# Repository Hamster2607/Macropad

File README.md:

This Macropad has 6 keys for media control and microphone with a rotary encoder for scrolling with qmk firmware. It also has an OLED display.

## Features

  -scrolling up/down
  -muting/unmuting the microphone
  -controlling media(e.g. skip track, pause, previous track)

## BOM
  
| Part                  | Quantity | Price (each) | Total   | Notes                        

 Seeed XIAO RP2040      1       | $6.50        | $6.50   Main MCU                      
 Switches with keycaps  5       | $0.50        | $2.50   TS-style, direct pin          
 Rotary encoder w/button  1     | $1.20        | $1.20   3-pin encoder                 
 3D-printed case        1 set   | $2.00        | $2.00   PLA, ~50 g 
 
Total : ~12.20 USD

## Layout

| SW1 (Undo) | SW2 (Prev) | SW6 (Next) |

| S1 (Mute)  | SW4 (Enter)| SW5 (Play) |

## PCB
This is the schematic for the PCB, made in KiCad

And this is the footprint

## Case

The case will be held tight by 4 M3x16 mm screws and it can be fuly 3D printed

## Full assembly(couldn't put switches in the model, get a hold of your imagination)

The XIAO RP2040 will stay under the PCB, to save space while being fully accessible trough the side

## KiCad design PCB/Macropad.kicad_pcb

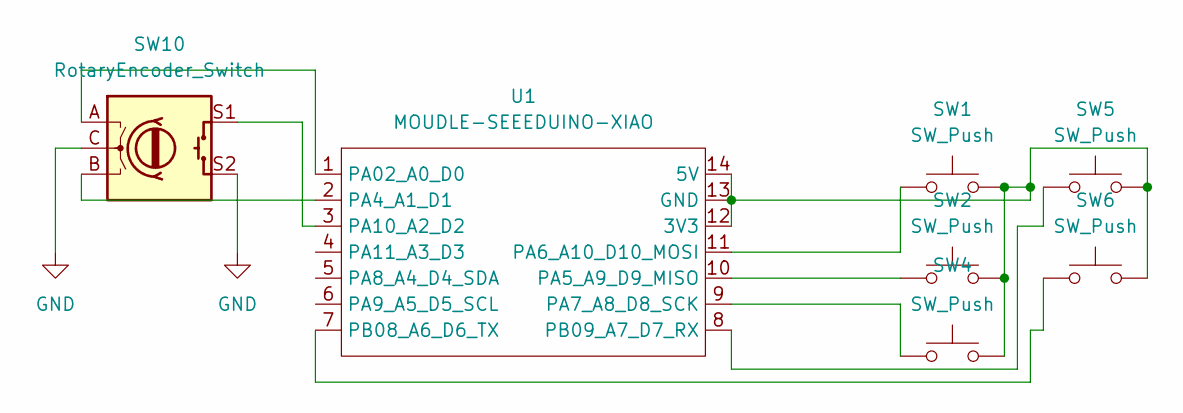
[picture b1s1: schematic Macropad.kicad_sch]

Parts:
SW1, SW2, SW4, SW5, SW6: SW_Push; SW_Cherry_MX_1.00u_PCB
SW10: RotaryEncoder_Switch; RotaryEncoder_Alps_EC11E-Switch_Vertical_H20mm
U1: MOUDLE-SEEEDUINO-XIAO; XIAO-Generic-Hybrid-14P-2.54-21X17.8MM

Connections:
GND: SW10.C, SW10.S2
unnamed: SW1.2, SW2.2, SW4.2, SW5.2, SW6.2, U1.12 (3V3), U1.13 (GND), U1.14 (5V)
unnamed: SW10.A, U1.1 (PA02_A0_D0)
unnamed: SW10.B, U1.2 (PA4_A1_D1)
unnamed: SW2.1, U1.10 (PA5_A9_D9_MISO)
unnamed: SW1.1, U1.11 (PA6_A10_D10_MOSI)
unnamed: SW4.1, U1.9 (PA7_A8_D8_SCK)
unnamed: SW10.S1, U1.3 (PA10_A2_D2)
unnamed: SW6.1, U1.7 (PB08_A6_D6_TX)
unnamed: SW5.1, U1.8 (PB09_A7_D7_RX)

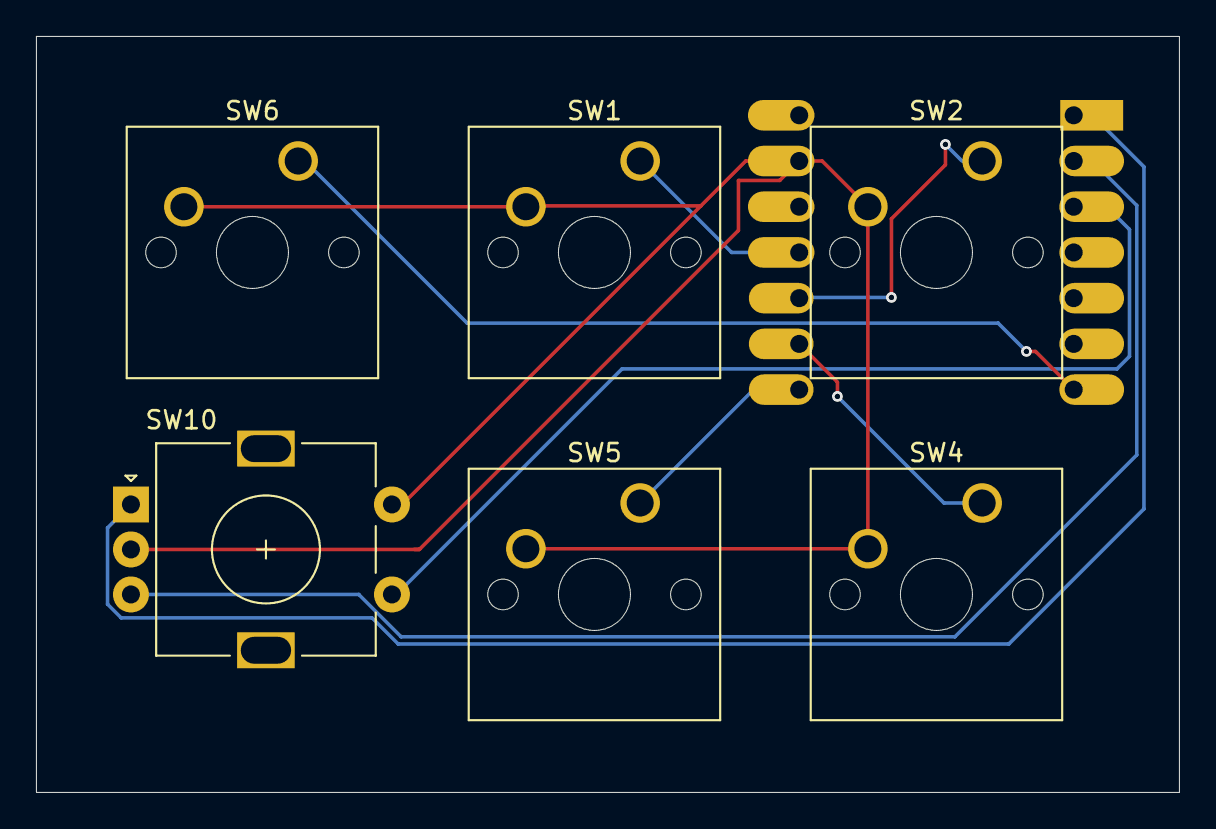
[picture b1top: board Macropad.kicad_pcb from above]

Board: 2 copper layers, 63.5 x 42.0 mm, 7 parts (1 on the bottom side), 10 nets.

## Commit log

2026-02-19 Fixed names
2026-02-19 Fixed names again....
2026-02-20 Added the compiled firmware and also the source code
2026-02-20 Added a readme
    Added detailed information about the Macropad project, including features, BOM, layout, PCB schematics, and case design.
2026-02-20 Fix image paths in README.md
    Updated image references for schematic, footprint, and case in README.
2026-02-20 Fix image references in README.md
2026-02-20 New case
2026-02-23 Case design update, PCB tweaks
2026-02-23 Add full assembly section to README
    Added section on full assembly with images.
2026-02-23 Updated Readme
    Added note about the XIAO RP2040 placement under the PCB.
2026-02-23 PCB tweaks
2026-02-27 Remade PCB and case
